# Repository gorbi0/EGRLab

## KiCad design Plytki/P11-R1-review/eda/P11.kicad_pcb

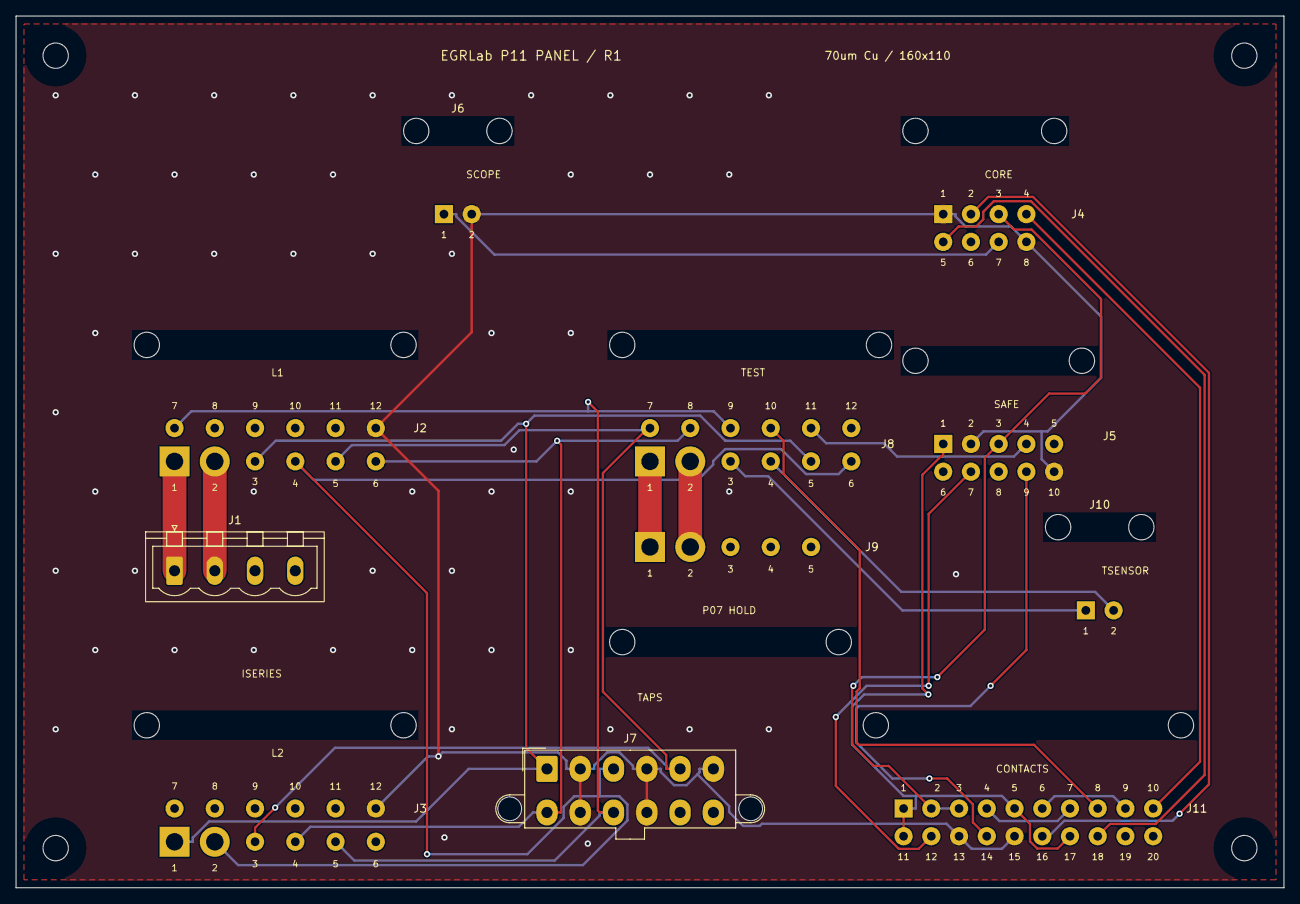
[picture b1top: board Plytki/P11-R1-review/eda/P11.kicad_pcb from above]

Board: 2 copper layers, 160.0 x 110.0 mm, 15 parts (0 on the bottom side), 24 nets.

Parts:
H1, H2, H3, H4: M3 NPTH
J1: ISERIES / P06; PhoenixContact_MSTBVA_2,5_4-G-5,08_1x04_P5.08mm_Vertical
J2: L1 tail; PTH_DT12
J3: L2 tail; PTH_DT12
J4: PANELCORE; PTH_CORE8
J5: PANELSAFE; PTH_SAFE10
J6: SCOPE tail; PTH_PAIR2
J7: TAPS / P05; Molex_Mini-Fit_Jr_5566-12A2_2x06_P4.20mm_Vertical
J8: TEST tail; PTH_DT12
J9: TMOTOR / HOLD; PTH_MOTOR5
J10: TSENSOR / P08; PTH_PAIR2
J11: CONTACTS / panel; PTH_CONTACT20

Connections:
/5V_SENSOR: J8.3, J10.1
/AGND_SENSOR: J8.4, J10.2
/CONTROL/N_J_SCOPE_HOT: J4.7, J6.1
/ECU_P1: J1.1, J2.1
/EGR_P1: J1.2, J2.2
/T_EGR_P1: J8.1, J9.1
/T_EGR_P3: J8.2, J9.2
ARM_CONTACT: J5.9, J11.14
DIAG_L1_L2: J11.6, J11.9
GND: J2.12, J3.12, J4.1, J4.8, J5.2, J5.10, J6.2, J7.2, J7.4, J7.6, J7.8, J7.10, J11.13, J11.15
ILK_L1_L2: J11.4, J11.7
LOGGER_CLEAR: J4.4, J11.10
LOOP_OUT: J8.10, J11.8
MARK: J4.2, J11.16
MECH_OK: J5.4, J8.11
PANEL_3V3: J5.1, J11.1, J11.5, J11.11, J11.17
STOP_NC_OUT: J5.7, J11.12
TAP_P1: J2.3, J3.1, J7.1, J8.5
TAP_P3: J2.4, J3.2, J7.3, J8.6
TAP_P4: J2.5, J3.3, J7.5, J8.7
TAP_P5: J2.6, J3.4, J7.7, J8.8
TAP_P6: J2.7, J3.5, J7.9, J8.9
TEST_KEY: J4.3, J5.3, J11.2, J11.3
TEST_PRESENT: J4.5, J11.18

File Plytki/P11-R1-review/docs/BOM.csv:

ref;source_ref;display;mpn;qty;footprint;on_board;url;note
J1;J1;ISERIES / P06;Phoenix 1755752;1;Connector_Phoenix_MSTB:PhoenixContact_MSTBVA_2,5_4-G-5,08_1x04_P5.08mm_Vertical;True;https://www.phoenixcontact.com/en-gb/products/1755752;
J2;J2;L1 tail;Soldered PTH harness;1;P11:PTH_DT12;True;;
J3;J3;L2 tail;Soldered PTH harness;1;P11:PTH_DT12;True;;
J8;J8;TEST tail;Soldered PTH harness;1;P11:PTH_DT12;True;;
X2;J2;DT04-12PB;DT04-12PB;1;P11:OFFBOARD;False;https://www.te.com/en/product-DT04-12PB.html;OFFBOARD: cavity numbers, not pin positions on PTH. Separate harness mapping required.
X3;J3;DT04-12PC;DT04-12PC;1;P11:OFFBOARD;False;https://www.te.com/en/product-DT04-12PC.html;OFFBOARD: cavity numbers, not pin positions on PTH. Separate harness mapping required.
X8;J8;DT04-12PA;DT04-12PA;1;P11:OFFBOARD;False;https://www.te.com/en/product-DT04-12PA.html;OFFBOARD: cavity numbers, not pin positions on PTH. Separate harness mapping required.
J4;J4;PANELCORE;Soldered harness;1;P11:PTH_CORE8;True;;
J5;J5;PANELSAFE;Soldered harness;1;P11:PTH_SAFE10;True;;
J6;J6_TAIL;SCOPE tail;RG174 100mm;1;P11:PTH_PAIR2;True;;
X6;J6;SCOPE BNC;Insulated panel BNC solder cup;1;P11:OFFBOARD;False;;"1=center;2=shell. High impedance 1Mohm only. Isolated from metal panel."
J7;J7;TAPS / P05;Molex 39-29-9129;1;Connector_Molex:Molex_Mini-Fit_Jr_5566-12A2_2x06_P4.20mm_Vertical;True;https://www.molex.com/en-us/products/part-detail/39299129;5566-12A2GS-210, pegs, gold. Match with P05 W2 50mm maximum.
J9;J9;TMOTOR / HOLD;Soldered 2x2.5mm2 harness;1;P11:PTH_MOTOR5;True;;P07 HOLD: unpopulated until purchased H bridge and P07 reviewed. No supply connection here.
J10;J10;TSENSOR / P08;Soldered harness;1;P11:PTH_PAIR2;True;;
J11;ADDED_CONTACT_TAIL;CONTACTS / panel;Soldered AWG24 harness;1;P11:PTH_CONTACT20;True;;Functional contact assignments in WIAZKI.md. Not IDC and no plug-in header.
X11;X11;ARM momentary NO;EAO 14-435.036 (reference low-level);1;P11:OFFBOARD;False;https://www.eao.com/component/14-435.036/en/actuator;"Functional terminal numbers in schematic; identify physical terminals from purchased part and continuity test. EAO reference is not a mandatory footprint. No illumination supply. Fixture and caps required."
X12;X12;L1 detector 2NC;EAO 14-432.036 (reference low-level);1;P11:OFFBOARD;False;https://www.eao.com/component/14-432.036/en/actuator;"Functional terminal numbers in schematic; identify physical terminals from purchased part and continuity test. EAO reference is not a mandatory footprint. No illumination supply. Fixture and caps required."
X13;X13;L2 detector 2NC;EAO 14-432.036 (reference low-level);1;P11:OFFBOARD;False;https://www.eao.com/component/14-432.036/en/actuator;"Functional terminal numbers in schematic; identify physical terminals from purchased part and continuity test. EAO reference is not a mandatory footprint. No illumination supply. Fixture and caps required."
X14;X14;MARK momentary NO;EAO 14-435.036 (reference low-level);1;P11:OFFBOARD;False;https://www.eao.com/component/14-435.036/en/actuator;"Functional terminal numbers in schematic; identify physical terminals from purchased part and continuity test. EAO reference is not a mandatory footprint. No illumination supply. Fixture and caps required."
X15;X15;KEY TEST NO;EAO 14-412.036K (reference low-level);1;P11:OFFBOARD;False;https://www.eao.com/component/14-412.036K/en/actuator;"Functional terminal numbers in schematic; identify physical terminals from purchased part and continuity test. EAO reference is not a mandatory footprint. No illumination supply. Fixture and caps required."
X16;X16;STOP latched NC+NO;EAO 14-473.036 (reference low-level);1;P11:OFFBOARD;False;https://www.eao.com/component/14-473.036/en/actuator;"Functional terminal numbers in schematic; identify physical terminals from purchased part and continuity test. EAO reference is not a mandatory footprint. No illumination supply. Fixture and caps required."
X17;X17;TEST detector NO;EAO 14-435.036 (reference low-level);1;P11:OFFBOARD;False;https://www.eao.com/component/14-435.036/en/actuator;"Functional terminal numbers in schematic; identify physical terminals from purchased part and continuity test. EAO reference is not a mandatory footprint. No illumination supply. Fixture and caps required."

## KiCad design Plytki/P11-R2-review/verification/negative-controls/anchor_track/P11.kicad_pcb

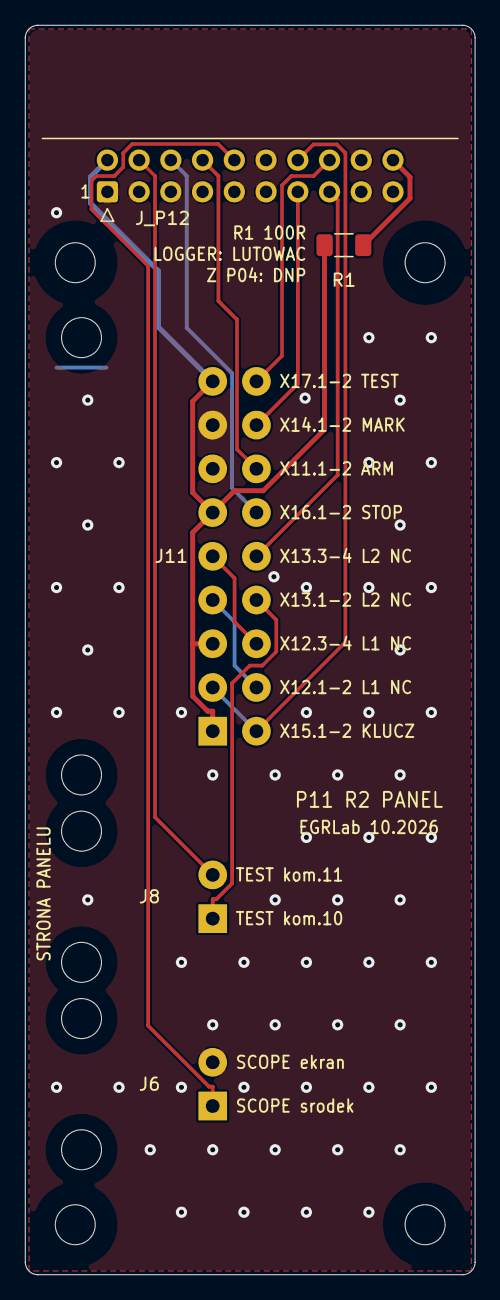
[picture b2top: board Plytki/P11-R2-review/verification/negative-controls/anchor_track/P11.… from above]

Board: 2 copper layers, 36.0 x 100.0 mm, 9 parts (0 on the bottom side), 14 nets.

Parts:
H1, H2, H3, H4: M3 NPTH
J6: SCOPE tail; FIELD_PAIR2
J8: TEST signal; FIELD_PAIR2
J11: CONTACTS; FIELD_CONTACT18
J_P12: IDC 2x10 katowe do P12; IDC-Header_2x10_P2.54mm_Horizontal
R1: 100R; R_1206_3216Metric_Pad1.30x1.75mm_HandSolder

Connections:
/3V3_IO: J_P12.20, R1.1
/CONTACTS/DIAG_L1_L2: J11.6, J11.9
/CONTACTS/ILK_L1_L2: J11.4, J11.7
/CONTACTS/LOOP_OUT: J8.1, J11.8
/N_J_SCOPE_HOT: J6.1, J_P12.10
ARM_CONTACT: J11.14, J_P12.8
GND: J6.2, J11.13, J11.15, J_P12.1, J_P12.3, J_P12.5, J_P12.7, J_P12.9, J_P12.11, J_P12.12, J_P12.17, J_P12.18, J_P12.19
LOGGER_CLEAR: J11.10, J_P12.15
MARK: J11.16, J_P12.13
MECH_OK: J8.2, J_P12.4
PANEL_3V3: J11.1, J11.5, J11.11, J11.17, J_P12.2, R1.2
STOP_NC_OUT: J11.12, J_P12.6
TEST_KEY: J11.2, J11.3, J_P12.14
TEST_PRESENT: J11.18, J_P12.16
